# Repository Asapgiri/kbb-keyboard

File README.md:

# Keyboard by KBB

## Summary
We are making this keyboard for self improvement and fun. The 65% mechanical keyboard has it's original PCB design, case and plate model.

## To open the shematics and PCB design
The PCB design was created in KiCad, so you can open it in the `kicad/default` folder.

## To run the code
You only need to upload the code once using Arduino IDE.

Keep in mind, that first the Atmega32u4 will need a bootloader, witch is programmed trough the bootloader pins. We had to program it with an Esp32-C3-mini, witches Arduino ISA codes I will upload here under the folder `Esp32-ISA`.

## Dependencies
Place the dependencies into the lib folder.
Desktop Utility:
--> simple_serial_port https://github.com/dmicha16/simple_serial_port/tree/master

## Layout

In this image the different colors mean the segmentation of the keys with muxes.
You can currently only see the details in Schematic and the Code files.

## Function keys
### Supported
| Combination | Meaning  |     | Combination | Meaning  |     | Combination | Meaning  |
| ---         | ---      | --- | ---         | ---      | --- | ---         | ---      |
| FN + 1      | F1       |     | FN + 7      | F7       |     | FN + INS    | PRT SCR  |
| FN + 2      | F2       |     | FN + 8      | F8       |     | FN + WIN    | WIN LOCK |
| FN + 3      | F3       |     | FN + 9      | F9       |     | FN + ->     | FN LOCK  |
| FN + 4      | F4       |     | FN + 0      | F10      |     | FN + ALT    | MENU     |
| FN + 5      | F5       |     | FN + -      | F11      |     | FN + ESC    | `        |
| FN + 6      | F6       |     | FN + =      | F12      |     | FN + SHIFT + ESC | ~   |

## Under develpement
### These keys are yet not supported due to the incompatibility of `Keyboard.h`.
| Combination | Meaning     |
| ---         | ---         |
| FN + ;      | PREV MUSIC  |
| FN + \      | NEXT  MUSIC |
| FN + ,      | VOLUME DOWN |
| FN + .      | VOLUME UP   |
| FN + /      | PLAY        |
| FN + END    | SLEEP       |

### TODOs
- Position USB ports on keyboard
- Rewire LEDs and I2C
- Update README for CMake and programming of board

# Known issues
... Under develpement

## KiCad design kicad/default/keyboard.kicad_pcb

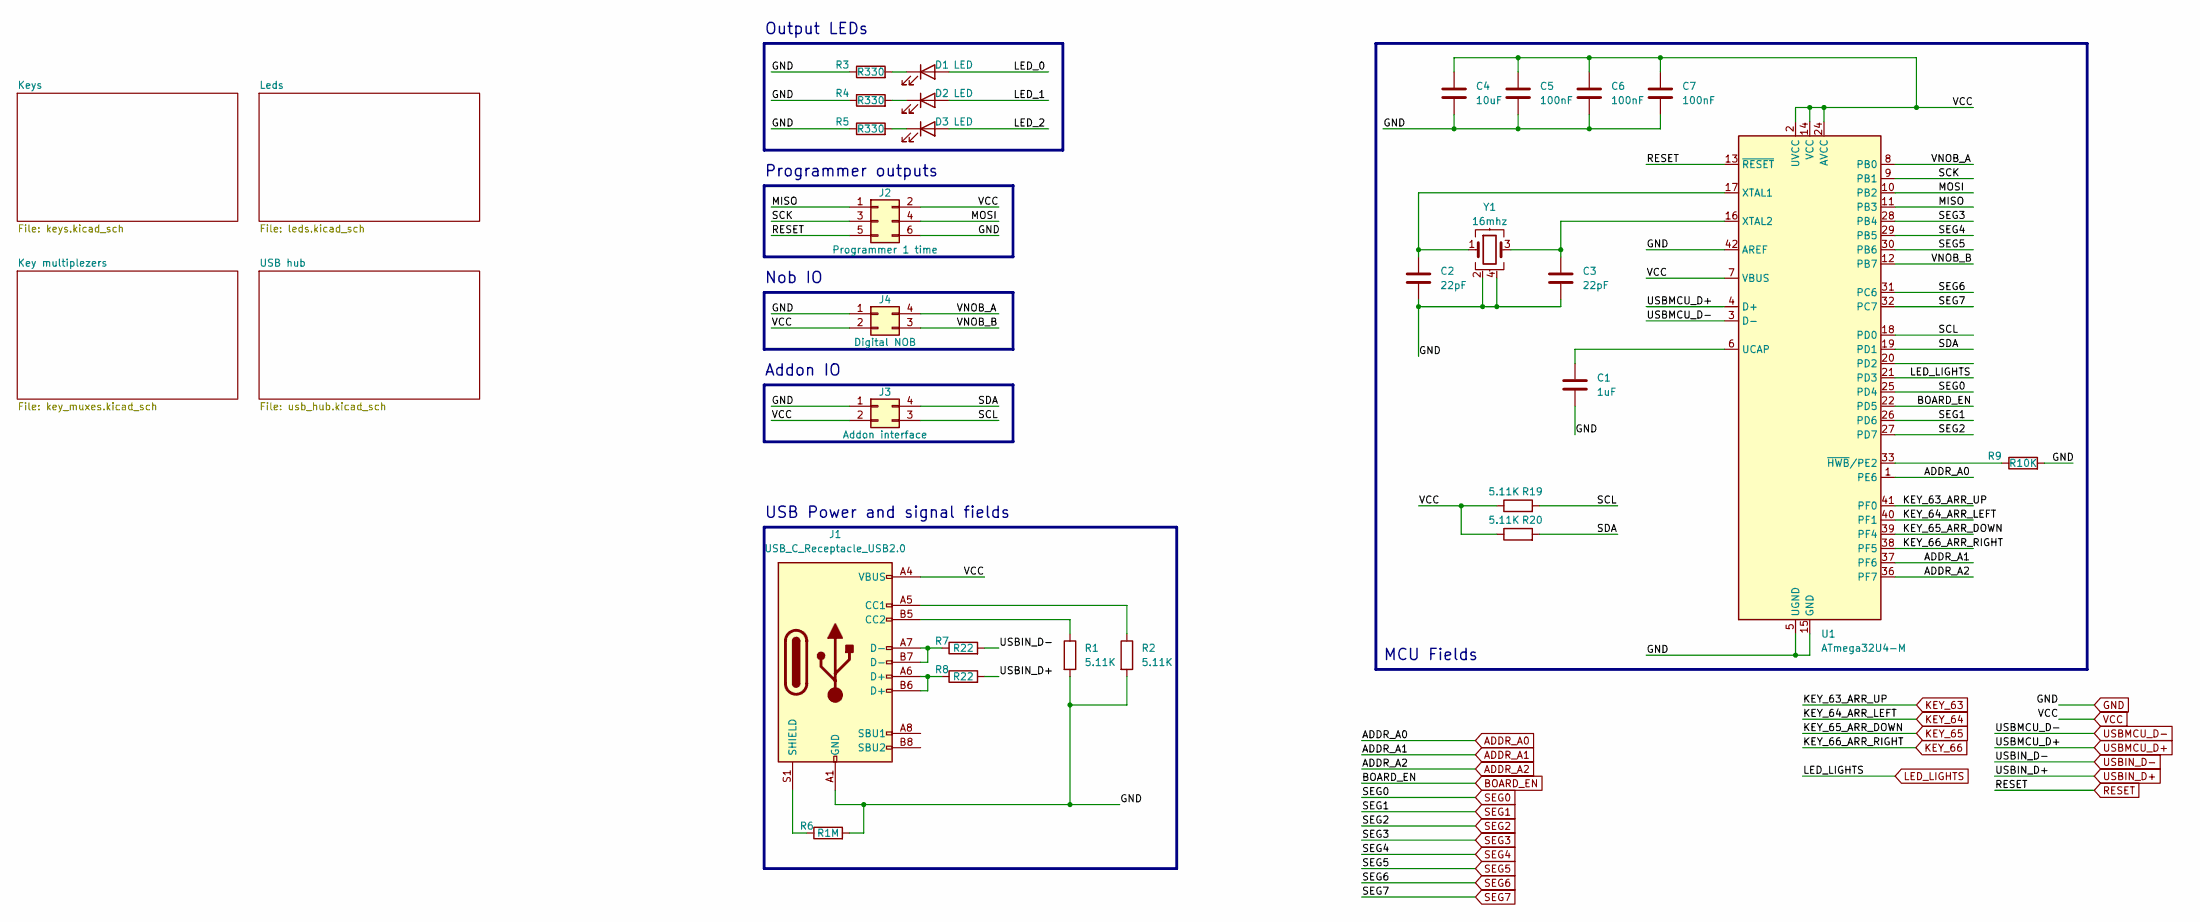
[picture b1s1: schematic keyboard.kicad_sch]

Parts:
C1: 1uF; C_0402_1005Metric
C2, C3: 22pF; C_0402_1005Metric
C4: 10uF; C_0402_1005Metric
C5, C6, C7: 100nF; C_0402_1005Metric
D1, D2, D3: LED; LED_D3.0mm_Clear
J1: USB_C_Receptacle_USB2.0; USB_C_Receptacle_G-Switch_GT-USB-7010ASV
J2: Programmer 1 time; PinHeader_2x03_P2.54mm_Vertical
J3: Addon interface; PinHeader_1x04_P2.54mm_Vertical
J4: Digital NOB; PinHeader_1x04_P2.54mm_Vertical
R1, R2, R19, R20: 5.11K; R_0402_1005Metric
R3, R4, R5: R330; R_0402_1005Metric
R6: R1M; R_0603_1608Metric
R7, R8: R22; R_0402_1005Metric
R9: R10K; R_0402_1005Metric
U1: ATmega32U4-M; QFN-44-1EP_7x7mm_P0.5mm_EP5.2x5.2mm
Y1: 16mhz; Crystal_SMD_7F16000E09UCG_4pin

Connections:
/MISO: J2.1, U1.11 (PB3)
/MOSI: J2.4, U1.10 (PB2)
/SCK: J2.3, U1.9 (PB1)
/SCL: J3.3, R19.2, U1.18 (PD0)
/SDA: J3.4, R20.2, U1.19 (PD1)
/VNOB_A: J4.4, U1.8 (PB0)
/VNOB_B: J4.3, U1.12 (PB7)
ADDR_A0: U1.1 (PE6); also elsewhere on the board
ADDR_A1: U1.37 (PF6); also elsewhere on the board
ADDR_A2: U1.36 (PF7); also elsewhere on the board
BOARD_EN: U1.22 (PD5); also elsewhere on the board
GND: C1.2, C2.2, C3.2, C4.2, C5.2, C6.2, C7.2, J1.A1 (GND), J1.A12 (GND), J1.B1 (GND), J1.B12 (GND), J2.6, J3.1, J4.1, R1.2, R2.2, R3.1, R4.1, R5.1, R6.2, R9.2, U1.5 (UGND), U1.15 (GND), U1.23 (GND), U1.35 (GND), U1.42 (AREF), U1.43 (GND), U1.45 (GND), Y1.2, Y1.4; also elsewhere on the board
KEY_63: U1.41 (PF0); also elsewhere on the board
KEY_64: U1.40 (PF1); also elsewhere on the board
KEY_65: U1.39 (PF4); also elsewhere on the board
KEY_66: U1.38 (PF5); also elsewhere on the board
LED_LIGHTS: U1.21 (PD3); also elsewhere on the board
unnamed: D1.1 (K), R3.2
unnamed: D2.1 (K), R4.2
unnamed: D3.1 (K), R5.2
unnamed: J1.A5 (CC1), R2.1
unnamed: J1.B5 (CC2), R1.1
unnamed: J1.A6 (D+), J1.B6 (D+), R8.1
unnamed: J1.A7 (D-), J1.B7 (D-), R7.1
unnamed: J1.S1 (SHIELD), R6.1
unnamed: C1.1, U1.6 (UCAP)
unnamed: C2.1, U1.17 (XTAL1), Y1.1
unnamed: C3.1, U1.16 (XTAL2), Y1.3
unnamed: R9.1, U1.33 (~HWB/PE2)
RESET: J2.5, U1.13 (~RESET); also elsewhere on the board
SEG0: U1.25 (PD4); also elsewhere on the board
SEG1: U1.26 (PD6); also elsewhere on the board
SEG2: U1.27 (PD7); also elsewhere on the board
SEG3: U1.28 (PB4); also elsewhere on the board
SEG4: U1.29 (PB5); also elsewhere on the board
SEG5: U1.30 (PB6); also elsewhere on the board
SEG6: U1.31 (PC6); also elsewhere on the board
SEG7: U1.32 (PC7); also elsewhere on the board
USBIN_D+: R8.2; also elsewhere on the board
USBIN_D-: R7.2; also elsewhere on the board
USBMCU_D+: U1.4 (D+); also elsewhere on the board
USBMCU_D-: U1.3 (D-); also elsewhere on the board
VCC: C4.1, C5.1, C6.1, C7.1, J1.A4 (VBUS), J1.A9 (VBUS), J1.B4 (VBUS), J1.B9 (VBUS), J2.2, J3.2, J4.2, R19.1, R20.1, U1.2 (UVCC), U1.7 (VBUS), U1.14 (VCC), U1.24 (AVCC), U1.34 (VCC), U1.44 (AVCC); also elsewhere on the board

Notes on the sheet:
MCU Fields
Programmer outputs
Nob IO
USB Power and signal fields
Output LEDs
Addon IO

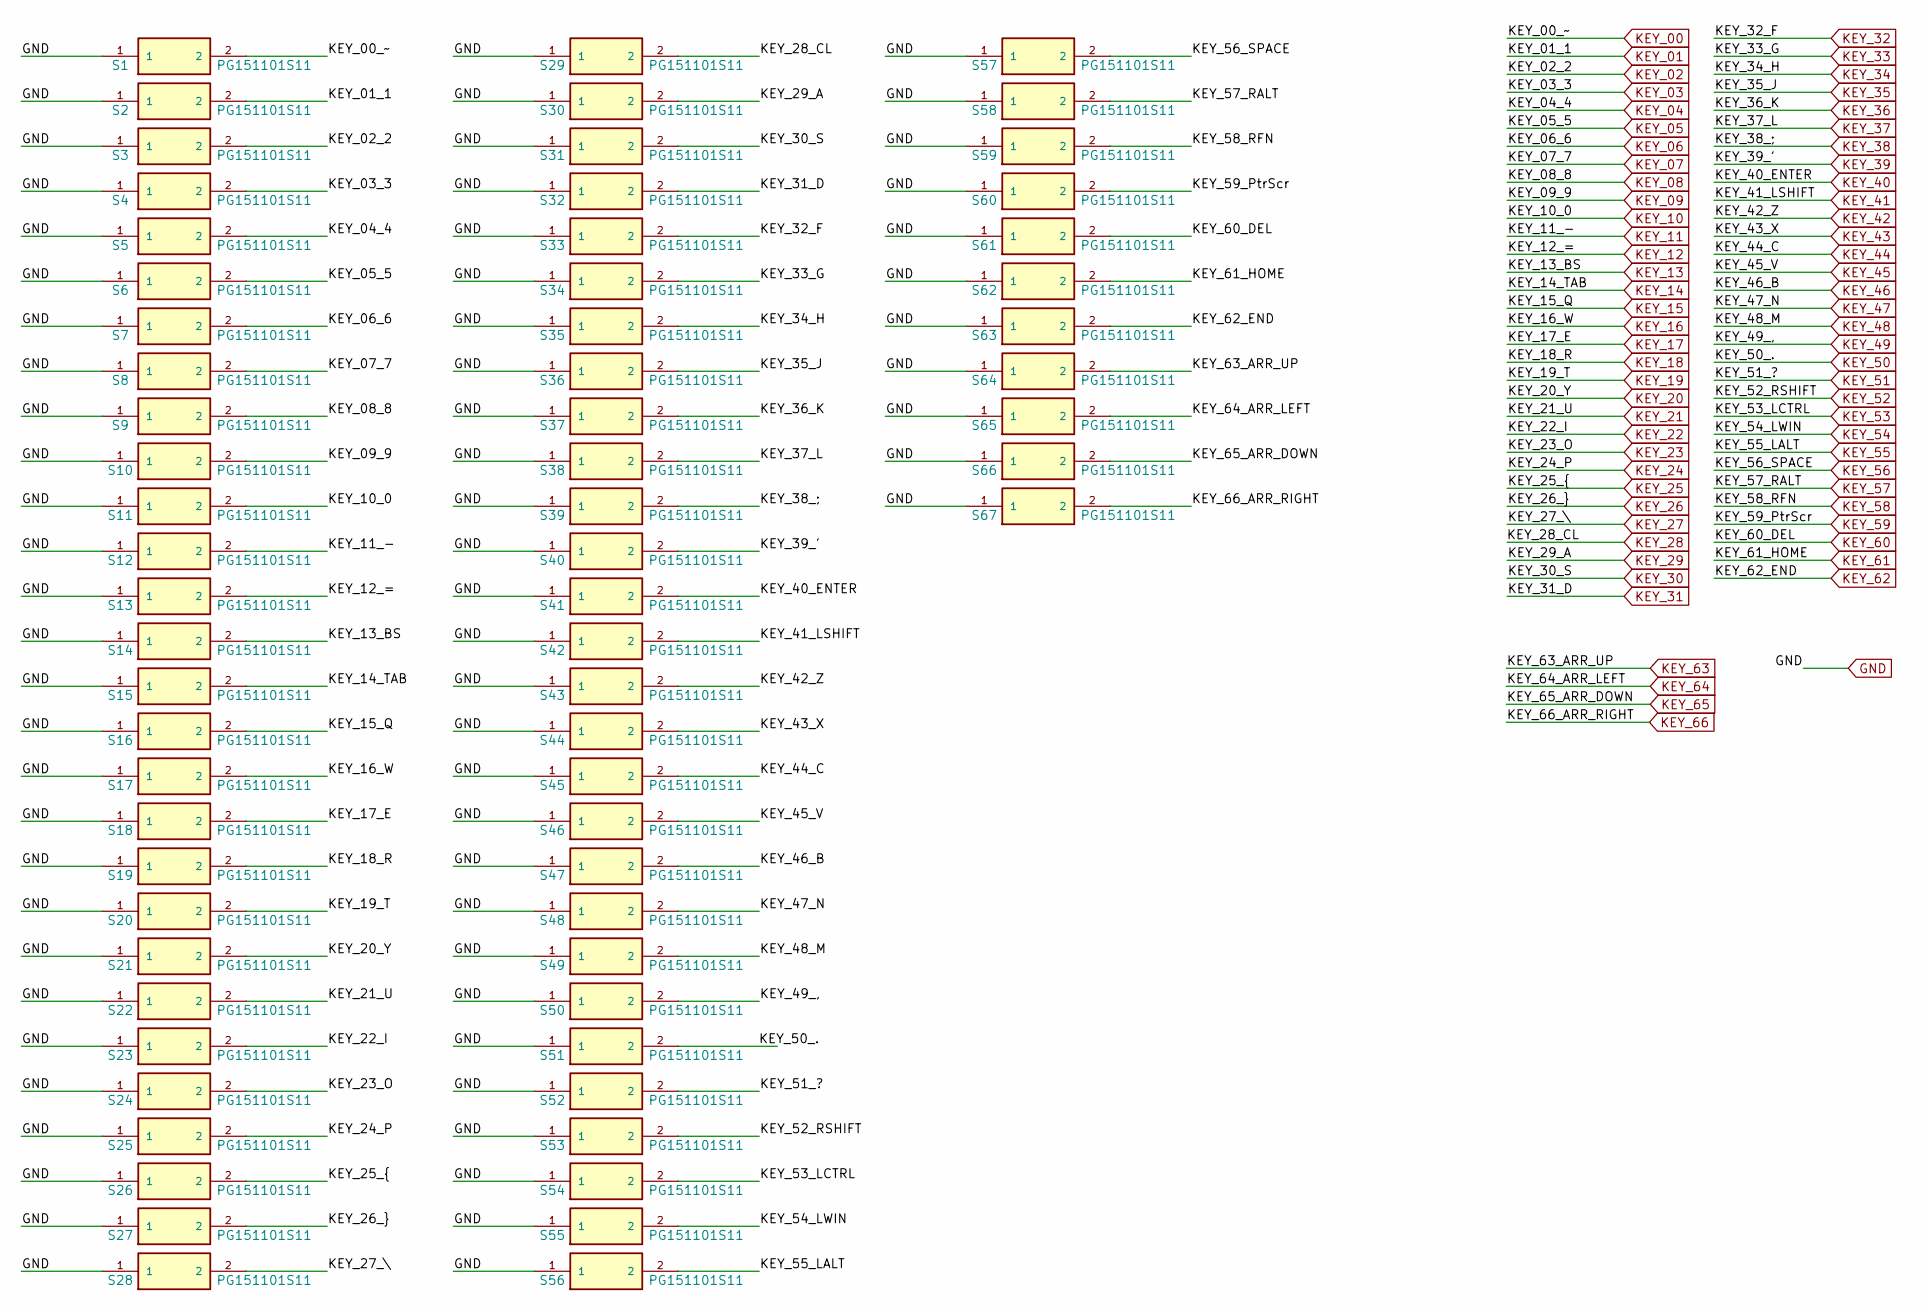
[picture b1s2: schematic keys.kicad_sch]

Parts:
S1, S2, S3, S4, S5, S6, S7, S8, S9, S10, S11, S12, S13, S17, S18, S19, S20, S21, S22, S23, S24, S25, S26, S27, S30, S31, S32, S33, S34, S35, S36, S37, S38, S39, S40, S43, S44, S45, S46, S47, S48, S49, S50, S51, S52, S60, S61, S62, S63, S64, S65, S66, S67: PG151101S11; SW_Cherry_MX_1.00u_PCB; PARTREV A
S14: PG151101S11; SW_Cherry_MX_2.00u_PCB; PARTREV A
S15, S28: PG151101S11; SW_Cherry_MX_1.50u_PCB; PARTREV A
S16: PG151101S11; SW_Cherry_MX_1.00u_PCB
S29, S53: PG151101S11; SW_Cherry_MX_1.75u_PCB; PARTREV A
S41, S42: PG151101S11; SW_Cherry_MX_2.25u_PCB; PARTREV A
S54, S55, S56, S58, S59: PG151101S11; SW_Cherry_MX_1.25u_PCB; PARTREV A
S57: PG151101S11; SW_Cherry_MX_6.25u_PCB; PARTREV A

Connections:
/Keys/KEY_28_CL: S29.2
GND: S1.1, S2.1, S3.1, S4.1, S5.1, S6.1, S7.1, S8.1, S9.1, S10.1, S11.1, S12.1, S13.1, S14.1, S15.1, S16.1, S17.1, S18.1, S19.1, S20.1, S21.1, S22.1, S23.1, S24.1, S25.1, S26.1, S27.1, S28.1, S29.1, S30.1, S31.1, S32.1, S33.1, S34.1, S35.1, S36.1, S37.1, S38.1, S39.1, S40.1, S41.1, S42.1, S43.1, S44.1, S45.1, S46.1, S47.1, S48.1, S49.1, S50.1, S51.1, S52.1, S53.1, S54.1, S55.1, S56.1, S57.1, S58.1, S59.1, S60.1, S61.1, S62.1, S63.1, S64.1, S65.1, S66.1, S67.1; also elsewhere on the board
KEY_00: S1.2; also elsewhere on the board
KEY_01: S2.2; also elsewhere on the board
KEY_02: S3.2; also elsewhere on the board
KEY_03: S4.2; also elsewhere on the board
KEY_04: S5.2; also elsewhere on the board
KEY_05: S6.2; also elsewhere on the board
KEY_06: S7.2; also elsewhere on the board
KEY_07: S8.2; also elsewhere on the board
KEY_08: S9.2; also elsewhere on the board
KEY_09: S10.2; also elsewhere on the board
KEY_10: S11.2; also elsewhere on the board
KEY_11: S12.2; also elsewhere on the board
KEY_12: S13.2; also elsewhere on the board
KEY_13: S14.2; also elsewhere on the board
KEY_14: S15.2; also elsewhere on the board
KEY_15: S16.2; also elsewhere on the board
KEY_16: S17.2; also elsewhere on the board
KEY_17: S18.2; also elsewhere on the board
KEY_18: S19.2; also elsewhere on the board
KEY_19: S20.2; also elsewhere on the board
KEY_20: S21.2; also elsewhere on the board
KEY_21: S22.2; also elsewhere on the board
KEY_22: S23.2; also elsewhere on the board
KEY_23: S24.2; also elsewhere on the board
KEY_24: S25.2; also elsewhere on the board
KEY_25: S26.2; also elsewhere on the board
KEY_26: S27.2; also elsewhere on the board
KEY_27: S28.2; also elsewhere on the board
KEY_29: S30.2; also elsewhere on the board
KEY_30: S31.2; also elsewhere on the board
KEY_31: S32.2; also elsewhere on the board
KEY_32: S33.2; also elsewhere on the board
KEY_33: S34.2; also elsewhere on the board
KEY_34: S35.2; also elsewhere on the board
KEY_35: S36.2; also elsewhere on the board
KEY_36: S37.2; also elsewhere on the board
KEY_37: S38.2; also elsewhere on the board
KEY_38: S39.2; also elsewhere on the board
KEY_39: S40.2; also elsewhere on the board
KEY_40: S41.2; also elsewhere on the board
KEY_41: S42.2; also elsewhere on the board
KEY_42: S43.2; also elsewhere on the board
KEY_43: S44.2; also elsewhere on the board
KEY_44: S45.2; also elsewhere on the board
KEY_45: S46.2; also elsewhere on the board
KEY_46: S47.2; also elsewhere on the board
KEY_47: S48.2; also elsewhere on the board
KEY_48: S49.2; also elsewhere on the board
KEY_49: S50.2; also elsewhere on the board
KEY_50: S51.2; also elsewhere on the board
KEY_51: S52.2; also elsewhere on the board
KEY_52: S53.2; also elsewhere on the board
KEY_53: S54.2; also elsewhere on the board
KEY_54: S55.2; also elsewhere on the board
KEY_55: S56.2; also elsewhere on the board
KEY_56: S57.2; also elsewhere on the board
KEY_57: S58.2; also elsewhere on the board
KEY_58: S59.2; also elsewhere on the board
KEY_59: S60.2; also elsewhere on the board
KEY_60: S61.2; also elsewhere on the board
KEY_61: S62.2; also elsewhere on the board
KEY_62: S63.2; also elsewhere on the board
KEY_63: S64.2; also elsewhere on the board
KEY_64: S65.2; also elsewhere on the board
KEY_65: S66.2; also elsewhere on the board
KEY_66: S67.2; also elsewhere on the board

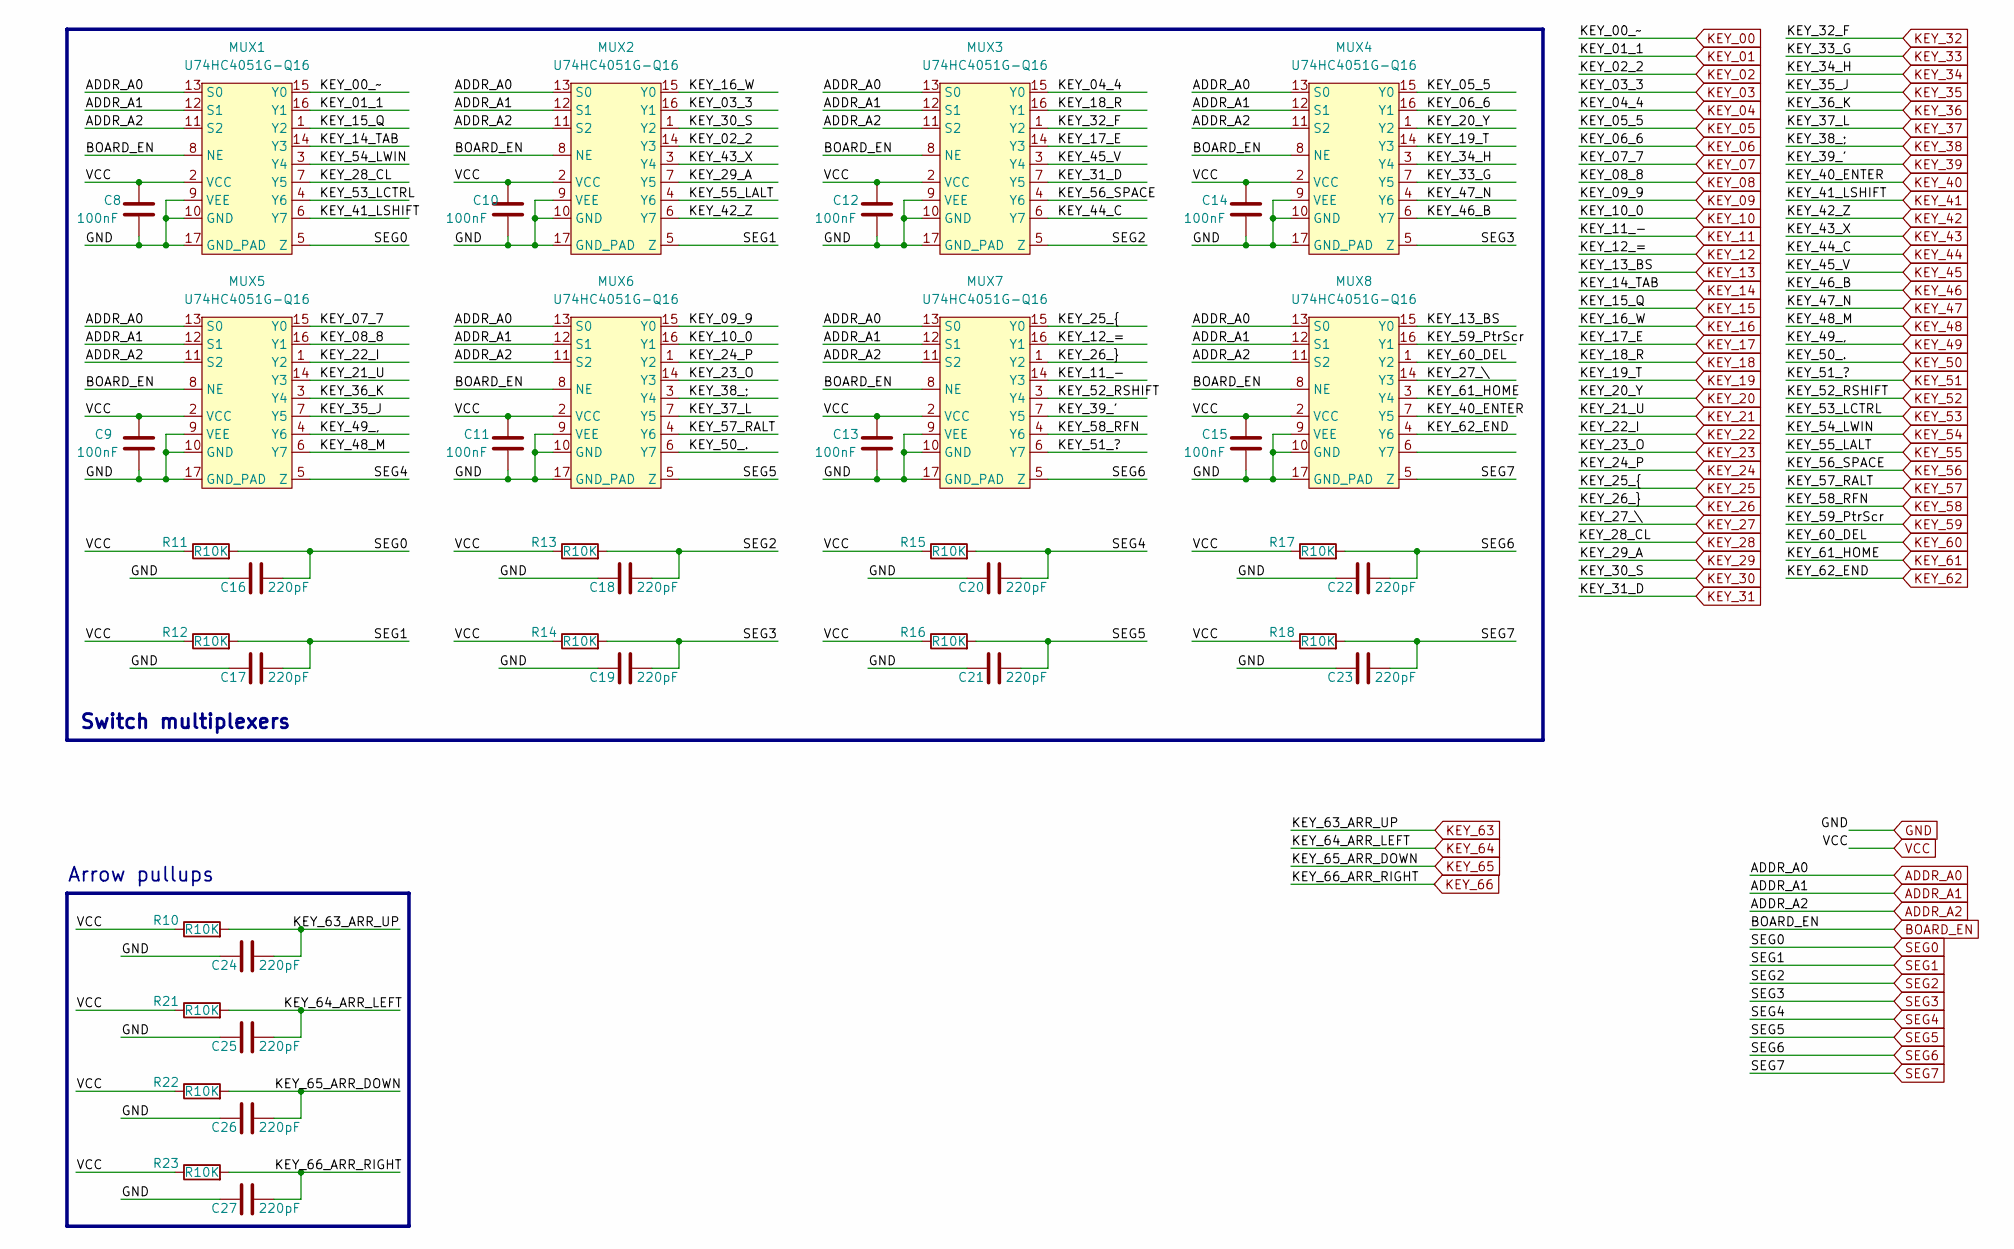
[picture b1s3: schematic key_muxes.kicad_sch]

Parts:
C8, C9, C10, C11, C12, C13, C14, C15: 100nF; C_0402_1005Metric
C16, C17, C18, C19, C20, C21, C22, C23, C24, C25, C26, C27: 220pF; C_0402_1005Metric
MUX1, MUX2, MUX3, MUX4, MUX5, MUX6, MUX7, MUX8: U74HC4051G-Q16; QFN-16-1EP_3x3mm_P0.5mm_EP1.7x1.7mm
R10, R11, R12, R13, R14, R15, R16, R17, R18, R21, R22, R23: R10K; R_0402_1005Metric

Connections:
/Key multiplezers/KEY_28_CL: MUX1.7 (Y5)
ADDR_A0: MUX1.13 (S0), MUX2.13 (S0), MUX3.13 (S0), MUX4.13 (S0), MUX5.13 (S0), MUX6.13 (S0), MUX7.13 (S0), MUX8.13 (S0); also elsewhere on the board
ADDR_A1: MUX1.12 (S1), MUX2.12 (S1), MUX3.12 (S1), MUX4.12 (S1), MUX5.12 (S1), MUX6.12 (S1), MUX7.12 (S1), MUX8.12 (S1); also elsewhere on the board
ADDR_A2: MUX1.11 (S2), MUX2.11 (S2), MUX3.11 (S2), MUX4.11 (S2), MUX5.11 (S2), MUX6.11 (S2), MUX7.11 (S2), MUX8.11 (S2); also elsewhere on the board
BOARD_EN: MUX1.8 (NE), MUX2.8 (NE), MUX3.8 (NE), MUX4.8 (NE), MUX5.8 (NE), MUX6.8 (NE), MUX7.8 (NE), MUX8.8 (NE); also elsewhere on the board
GND: C8.2, C9.2, C10.2, C11.2, C12.2, C13.2, C14.2, C15.2, C16.1, C17.1, C18.1, C19.1, C20.1, C21.1, C22.1, C23.1, C24.1, C25.1, C26.1, C27.1, MUX1.9 (VEE), MUX1.10 (GND), MUX1.17 (GND_PAD), MUX2.9 (VEE), MUX2.10 (GND), MUX2.17 (GND_PAD), MUX3.9 (VEE), MUX3.10 (GND), MUX3.17 (GND_PAD), MUX4.9 (VEE), MUX4.10 (GND), MUX4.17 (GND_PAD), MUX5.9 (VEE), MUX5.10 (GND), MUX5.17 (GND_PAD), MUX6.9 (VEE), MUX6.10 (GND), MUX6.17 (GND_PAD), MUX7.9 (VEE), MUX7.10 (GND), MUX7.17 (GND_PAD), MUX8.9 (VEE), MUX8.10 (GND), MUX8.17 (GND_PAD); also elsewhere on the board
KEY_00: MUX1.15 (Y0); also elsewhere on the board
KEY_01: MUX1.16 (Y1); also elsewhere on the board
KEY_02: MUX2.14 (Y3); also elsewhere on the board
KEY_03: MUX2.16 (Y1); also elsewhere on the board
KEY_04: MUX3.15 (Y0); also elsewhere on the board
KEY_05: MUX4.15 (Y0); also elsewhere on the board
KEY_06: MUX4.16 (Y1); also elsewhere on the board
KEY_07: MUX5.15 (Y0); also elsewhere on the board
KEY_08: MUX5.16 (Y1); also elsewhere on the board
KEY_09: MUX6.15 (Y0); also elsewhere on the board
KEY_10: MUX6.16 (Y1); also elsewhere on the board
KEY_11: MUX7.14 (Y3); also elsewhere on the board
KEY_12: MUX7.16 (Y1); also elsewhere on the board
KEY_13: MUX8.15 (Y0); also elsewhere on the board
KEY_14: MUX1.14 (Y3); also elsewhere on the board
KEY_15: MUX1.1 (Y2); also elsewhere on the board
KEY_16: MUX2.15 (Y0); also elsewhere on the board
KEY_17: MUX3.14 (Y3); also elsewhere on the board
KEY_18: MUX3.16 (Y1); also elsewhere on the board
KEY_19: MUX4.14 (Y3); also elsewhere on the board
KEY_20: MUX4.1 (Y2); also elsewhere on the board
KEY_21: MUX5.14 (Y3); also elsewhere on the board
KEY_22: MUX5.1 (Y2); also elsewhere on the board
KEY_23: MUX6.14 (Y3); also elsewhere on the board
KEY_24: MUX6.1 (Y2); also elsewhere on the board
KEY_25: MUX7.15 (Y0); also elsewhere on the board
KEY_26: MUX7.1 (Y2); also elsewhere on the board
KEY_27: MUX8.14 (Y3); also elsewhere on the board
KEY_29: MUX2.7 (Y5); also elsewhere on the board
KEY_30: MUX2.1 (Y2); also elsewhere on the board
KEY_31: MUX3.7 (Y5); also elsewhere on the board
KEY_32: MUX3.1 (Y2); also elsewhere on the board
KEY_33: MUX4.7 (Y5); also elsewhere on the board
KEY_34: MUX4.3 (Y4); also elsewhere on the board
KEY_35: MUX5.7 (Y5); also elsewhere on the board
KEY_36: MUX5.3 (Y4); also elsewhere on the board
KEY_37: MUX6.7 (Y5); also elsewhere on the board
KEY_38: MUX6.3 (Y4); also elsewhere on the board
KEY_39: MUX7.7 (Y5); also elsewhere on the board
KEY_40: MUX8.7 (Y5); also elsewhere on the board
KEY_41: MUX1.6 (Y7); also elsewhere on the board
KEY_42: MUX2.6 (Y7); also elsewhere on the board
KEY_43: MUX2.3 (Y4); also elsewhere on the board
KEY_44: MUX3.6 (Y7); also elsewhere on the board
KEY_45: MUX3.3 (Y4); also elsewhere on the board
KEY_46: MUX4.6 (Y7); also elsewhere on the board
KEY_47: MUX4.4 (Y6); also elsewhere on the board
KEY_48: MUX5.6 (Y7); also elsewhere on the board
KEY_49: MUX5.4 (Y6); also elsewhere on the board
KEY_50: MUX6.6 (Y7); also elsewhere on the board
KEY_51: MUX7.6 (Y7); also elsewhere on the board
KEY_52: MUX7.3 (Y4); also elsewhere on the board
KEY_53: MUX1.4 (Y6); also elsewhere on the board
KEY_54: MUX1.3 (Y4); also elsewhere on the board
KEY_55: MUX2.4 (Y6); also elsewhere on the board
KEY_56: MUX3.4 (Y6); also elsewhere on the board
KEY_57: MUX6.4 (Y6); also elsewhere on the board
KEY_58: MUX7.4 (Y6); also elsewhere on the board
KEY_59: MUX8.16 (Y1); also elsewhere on the board
KEY_60: MUX8.1 (Y2); also elsewhere on the board
KEY_61: MUX8.3 (Y4); also elsewhere on the board
KEY_62: MUX8.4 (Y6); also elsewhere on the board
KEY_63: C24.2, R10.2; also elsewhere on the board
KEY_64: C25.2, R21.2; also elsewhere on the board
KEY_65: C26.2, R22.2; also elsewhere on the board
KEY_66: C27.2, R23.2; also elsewhere on the board
SEG0: C16.2, MUX1.5 (Z), R11.2; also elsewhere on the board
SEG1: C17.2, MUX2.5 (Z), R12.2; also elsewhere on the board
SEG2: C18.2, MUX3.5 (Z), R13.2; also elsewhere on the board
SEG3: C19.2, MUX4.5 (Z), R14.2; also elsewhere on the board
SEG4: C20.2, MUX5.5 (Z), R15.2; also elsewhere on the board
SEG5: C21.2, MUX6.5 (Z), R16.2; also elsewhere on the board
SEG6: C22.2, MUX7.5 (Z), R17.2; also elsewhere on the board
SEG7: C23.2, MUX8.5 (Z), R18.2; also elsewhere on the board
VCC: C8.1, C9.1, C10.1, C11.1, C12.1, C13.1, C14.1, C15.1, MUX1.2 (VCC), MUX2.2 (VCC), MUX3.2 (VCC), MUX4.2 (VCC), MUX5.2 (VCC), MUX6.2 (VCC), MUX7.2 (VCC), MUX8.2 (VCC), R10.1, R11.1, R12.1, R13.1, R14.1, R15.1, R16.1, R17.1, R18.1, R21.1, R22.1, R23.1; also elsewhere on the board

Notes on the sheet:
Arrow pullups
Switch multiplexers

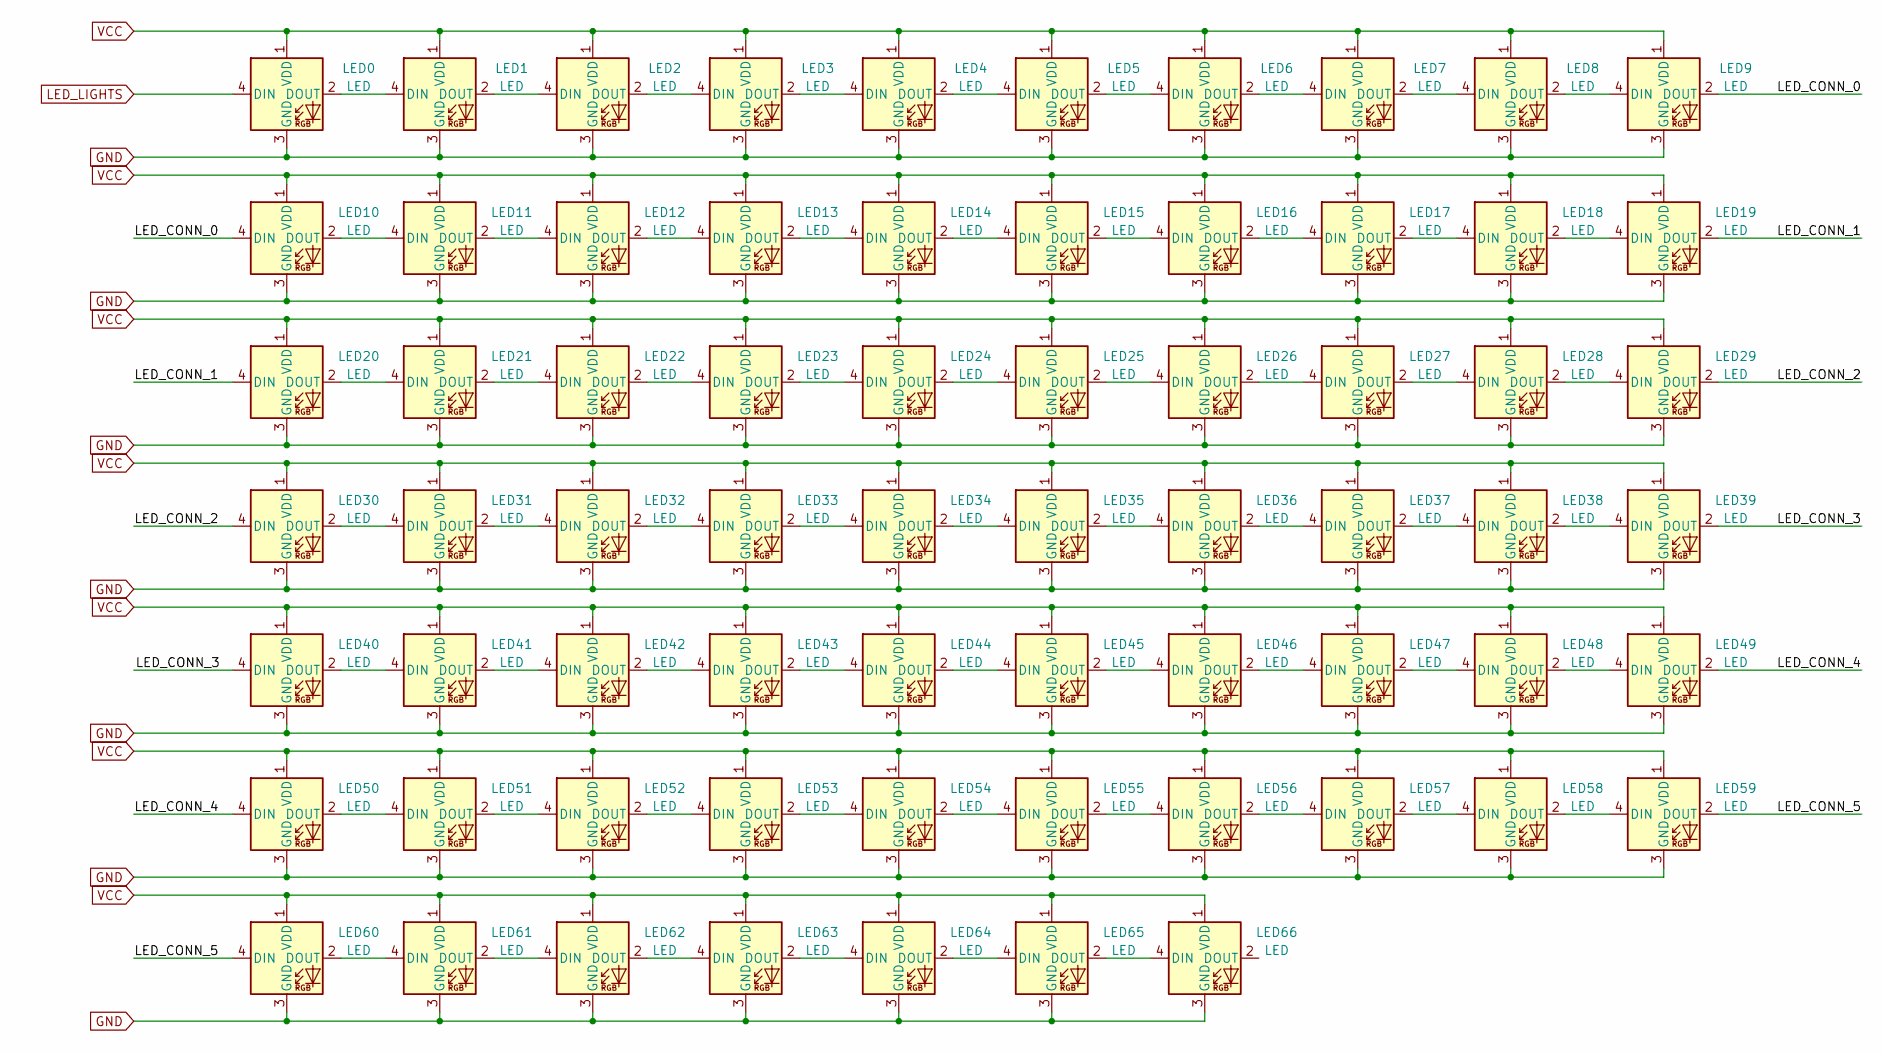
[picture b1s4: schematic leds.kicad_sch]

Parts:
LED0, LED1, LED2, LED3, LED4, LED5, LED6, LED7, LED8, LED9, LED10, LED11, LED12, LED13, LED14, LED15, LED16, LED17, LED18, LED19, LED20, LED21, LED22, LED23, LED24, LED25, LED26, LED27, LED28, LED29, LED30, LED31, LED32, LED33, LED34, LED35, LED36, LED37, LED38, LED39, LED40, LED41, LED42, LED43, LED44, LED45, LED46, LED47, LED48, LED49, LED50, LED51, LED52, LED53, LED54, LED55, LED56, LED57, LED58, LED59, LED60, LED61, LED62, LED63, LED64, LED65, LED66: LED; SK6812-MINI-E

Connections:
/Leds/LED_CONN_0: LED9.2 (DOUT), LED10.4 (DIN)
/Leds/LED_CONN_1: LED19.2 (DOUT), LED20.4 (DIN)
/Leds/LED_CONN_2: LED29.2 (DOUT), LED30.4 (DIN)
/Leds/LED_CONN_3: LED39.2 (DOUT), LED40.4 (DIN)
/Leds/LED_CONN_4: LED49.2 (DOUT), LED50.4 (DIN)
/Leds/LED_CONN_5: LED59.2 (DOUT), LED60.4 (DIN)
GND: LED0.3 (GND), LED1.3 (GND), LED2.3 (GND), LED3.3 (GND), LED4.3 (GND), LED5.3 (GND), LED6.3 (GND), LED7.3 (GND), LED8.3 (GND), LED9.3 (GND), LED10.3 (GND), LED11.3 (GND), LED12.3 (GND), LED13.3 (GND), LED14.3 (GND), LED15.3 (GND), LED16.3 (GND), LED17.3 (GND), LED18.3 (GND), LED19.3 (GND), LED20.3 (GND), LED21.3 (GND), LED22.3 (GND), LED23.3 (GND), LED24.3 (GND), LED25.3 (GND), LED26.3 (GND), LED27.3 (GND), LED28.3 (GND), LED29.3 (GND), LED30.3 (GND), LED31.3 (GND), LED32.3 (GND), LED33.3 (GND), LED34.3 (GND), LED35.3 (GND), LED36.3 (GND), LED37.3 (GND), LED38.3 (GND), LED39.3 (GND), LED40.3 (GND), LED41.3 (GND), LED42.3 (GND), LED43.3 (GND), LED44.3 (GND), LED45.3 (GND), LED46.3 (GND), LED47.3 (GND), LED48.3 (GND), LED49.3 (GND), LED50.3 (GND), LED51.3 (GND), LED52.3 (GND), LED53.3 (GND), LED54.3 (GND), LED55.3 (GND), LED56.3 (GND), LED57.3 (GND), LED58.3 (GND), LED59.3 (GND), LED60.3 (GND), LED61.3 (GND), LED62.3 (GND), LED63.3 (GND), LED64.3 (GND), LED65.3 (GND), LED66.3 (GND); also elsewhere on the board
LED_LIGHTS: LED0.4 (DIN); also elsewhere on the board
unnamed: LED0.2 (DOUT), LED1.4 (DIN)
unnamed: LED1.2 (DOUT), LED2.4 (DIN)
unnamed: LED2.2 (DOUT), LED3.4 (DIN)
unnamed: LED3.2 (DOUT), LED4.4 (DIN)
unnamed: LED4.2 (DOUT), LED5.4 (DIN)
unnamed: LED5.2 (DOUT), LED6.4 (DIN)
unnamed: LED6.2 (DOUT), LED7.4 (DIN)
unnamed: LED7.2 (DOUT), LED8.4 (DIN)
unnamed: LED8.2 (DOUT), LED9.4 (DIN)
unnamed: LED10.2 (DOUT), LED11.4 (DIN)
unnamed: LED11.2 (DOUT), LED12.4 (DIN)
unnamed: LED12.2 (DOUT), LED13.4 (DIN)
unnamed: LED13.2 (DOUT), LED14.4 (DIN)
unnamed: LED14.2 (DOUT), LED15.4 (DIN)
unnamed: LED15.2 (DOUT), LED16.4 (DIN)
unnamed: LED16.2 (DOUT), LED17.4 (DIN)
unnamed: LED17.2 (DOUT), LED18.4 (DIN)
unnamed: LED18.2 (DOUT), LED19.4 (DIN)
unnamed: LED20.2 (DOUT), LED21.4 (DIN)
unnamed: LED21.2 (DOUT), LED22.4 (DIN)
unnamed: LED22.2 (DOUT), LED23.4 (DIN)
unnamed: LED23.2 (DOUT), LED24.4 (DIN)
unnamed: LED24.2 (DOUT), LED25.4 (DIN)
unnamed: LED25.2 (DOUT), LED26.4 (DIN)
unnamed: LED26.2 (DOUT), LED27.4 (DIN)
unnamed: LED27.2 (DOUT), LED28.4 (DIN)
unnamed: LED28.2 (DOUT), LED29.4 (DIN)
unnamed: LED30.2 (DOUT), LED31.4 (DIN)
unnamed: LED31.2 (DOUT), LED32.4 (DIN)
unnamed: LED32.2 (DOUT), LED33.4 (DIN)
unnamed: LED33.2 (DOUT), LED34.4 (DIN)
unnamed: LED34.2 (DOUT), LED35.4 (DIN)
unnamed: LED35.2 (DOUT), LED36.4 (DIN)
unnamed: LED36.2 (DOUT), LED37.4 (DIN)
unnamed: LED37.2 (DOUT), LED38.4 (DIN)
unnamed: LED38.2 (DOUT), LED39.4 (DIN)
unnamed: LED40.2 (DOUT), LED41.4 (DIN)
unnamed: LED41.2 (DOUT), LED42.4 (DIN)
unnamed: LED42.2 (DOUT), LED43.4 (DIN)
unnamed: LED43.2 (DOUT), LED44.4 (DIN)
unnamed: LED44.2 (DOUT), LED45.4 (DIN)
unnamed: LED45.2 (DOUT), LED46.4 (DIN)
unnamed: LED46.2 (DOUT), LED47.4 (DIN)
unnamed: LED47.2 (DOUT), LED48.4 (DIN)
unnamed: LED48.2 (DOUT), LED49.4 (DIN)
unnamed: LED50.2 (DOUT), LED51.4 (DIN)
unnamed: LED51.2 (DOUT), LED52.4 (DIN)
unnamed: LED52.2 (DOUT), LED53.4 (DIN)
unnamed: LED53.2 (DOUT), LED54.4 (DIN)
unnamed: LED54.2 (DOUT), LED55.4 (DIN)
unnamed: LED55.2 (DOUT), LED56.4 (DIN)
unnamed: LED56.2 (DOUT), LED57.4 (DIN)
unnamed: LED57.2 (DOUT), LED58.4 (DIN)
unnamed: LED58.2 (DOUT), LED59.4 (DIN)
unnamed: LED60.2 (DOUT), LED61.4 (DIN)
unnamed: LED61.2 (DOUT), LED62.4 (DIN)
unnamed: LED62.2 (DOUT), LED63.4 (DIN)
unnamed: LED63.2 (DOUT), LED64.4 (DIN)
unnamed: LED64.2 (DOUT), LED65.4 (DIN)
unnamed: LED65.2 (DOUT), LED66.4 (DIN)
VCC: LED0.1 (VDD), LED1.1 (VDD), LED2.1 (VDD), LED3.1 (VDD), LED4.1 (VDD), LED5.1 (VDD), LED6.1 (VDD), LED7.1 (VDD), LED8.1 (VDD), LED9.1 (VDD), LED10.1 (VDD), LED11.1 (VDD), LED12.1 (VDD), LED13.1 (VDD), LED14.1 (VDD), LED15.1 (VDD), LED16.1 (VDD), LED17.1 (VDD), LED18.1 (VDD), LED19.1 (VDD), LED20.1 (VDD), LED21.1 (VDD), LED22.1 (VDD), LED23.1 (VDD), LED24.1 (VDD), LED25.1 (VDD), LED26.1 (VDD), LED27.1 (VDD), LED28.1 (VDD), LED29.1 (VDD), LED30.1 (VDD), LED31.1 (VDD), LED32.1 (VDD), LED33.1 (VDD), LED34.1 (VDD), LED35.1 (VDD), LED36.1 (VDD), LED37.1 (VDD), LED38.1 (VDD), LED39.1 (VDD), LED40.1 (VDD), LED41.1 (VDD), LED42.1 (VDD), LED43.1 (VDD), LED44.1 (VDD), LED45.1 (VDD), LED46.1 (VDD), LED47.1 (VDD), LED48.1 (VDD), LED49.1 (VDD), LED50.1 (VDD), LED51.1 (VDD), LED52.1 (VDD), LED53.1 (VDD), LED54.1 (VDD), LED55.1 (VDD), LED56.1 (VDD), LED57.1 (VDD), LED58.1 (VDD), LED59.1 (VDD), LED60.1 (VDD), LED61.1 (VDD), LED62.1 (VDD), LED63.1 (VDD), LED64.1 (VDD), LED65.1 (VDD), LED66.1 (VDD); also elsewhere on the board
